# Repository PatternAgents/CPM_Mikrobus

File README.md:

CPM_Mikrobus Adaptor
====================

PatternAgents CPM_Mikrobus Adaptor

[  
*PatternAgents CPM_Mikrobus Adaptor*](http://www.patternagents.com/projects/CPM_Mikrobus.html)

The "CPM_Mikrobus Adaptor" board is designed to enable Cypress PSoC development boards to utilize Mikrobus peripherals.

The PatternAgents "CPM_Mikrobus Adaptor" board supports :

Cypress CY8CKIT-001 : (Supports up to three (3) "CPM_Mikrobus Adaptor")

Cypress CY8CKIT-030 : (Supports up to two (2) "CPM_Mikrobus Adaptor")

Cypress CY8CKIT-050 : (Supports up to two (2) "CPM_Mikrobus Adaptor")

Cypress CY3280-28xxx : (Supports one (1) "CPM_Mikrobus Adaptor")

Cypress CY3280-22x45 : (Supports one (1) "CPM_Mikrobus Adaptor")

(Not an Exhaustive list as more Cypress development boards are routinely released)

For information on Mikrobus peripherals, see http://www.mikroe.com/mikrobus/

[  
*Licensing CC BY-NC-SA 4.0*](http://creativecommons.org/licenses/by-nc-sa/4.0/)

PatternAgents uses the increasingly popular business model called "Dual Licensing" 
in which both the open source software distribution mechanism and traditional commercial software distribution models are combined.

Open Source Projects:        

If you are developing and distributing open source applications under the Creative Commons CC BY-NC-SA 4.0, 
as published by the Creative Commons Foundation, then you are free to use the PatternAgents hardware/software under the CC BY-NC-SA 4.0 license. 
Please note that CC BY-NC-SA 4.0 requires that all modifications to the original code as well as all Derivative Works 
must also be released under the terms of the CC BY-NC-SA 4.0 license.

Closed Source Projects:

If you are developing and distributing traditional closed source or commercial applications, 
you must purchase a PatternAgents commercial use license, 
which is specifically designed for users interested in retaining the proprietary status of their designs and code. 
All PatternAgents commercial licenses expressly supersede the CC BY-NC-SA 4.0 license. 
This means that when you license the PatternAgents software under a commercial license, 
you specifically do not use the software under the CC BY-NC-SA 4.0 license and therefore you are not subject to any of its terms.
        
If you would like to use our designs for your own personal or educational use, have at it! 

Our public design repository is available at <a href="https://github.com/patternagents">Github</a>.

If you would like to produce our designs for commercial use, or as products for sale, 
please contact us to arrange for a Commercial Use license. We have many other designs, 
as well as options and extras that are not released publicly. 
We will also customize designs, firmware, and software for a reasonable fee, just contact us to discuss your requirements.

THIS SOFTWARE IS PROVIDED BY THE CONTRIBUTORS "AS IS" AND WITHOUT ANY EXPRESS OR IMPLIED WARRANTIES, 
INCLUDING, BUT NOT LIMITED TO, THE IMPLIED WARRANTIES OF MERCHANTABILITY AND FITNESS FOR A PARTICULAR PURPOSE ARE DISCLAIMED. 
IN NO EVENT SHALL THE COPYRIGHT OWNER OR CONTRIBUTORS BE LIABLE FOR ANY DIRECT, INDIRECT, INCIDENTAL, SPECIAL, EXEMPLARY, 
OR CONSEQUENTIAL DAMAGES (INCLUDING, BUT NOT LIMITED TO, PROCUREMENT OF SUBSTITUTE GOODS OR SERVICES; LOSS OF USE, DATA, 
OR PROFITS; OR BUSINESS INTERRUPTION) HOWEVER CAUSED AND ON ANY THEORY OF LIABILITY, WHETHER IN CONTRACT, 
STRICT LIABILITY, OR TORT (INCLUDING NEGLIGENCE OR OTHERWISE) ARISING IN ANY WAY OUT OF THE USE OF THIS SOFTWARE, 
EVEN IF ADVISED OF THE POSSIBILITY OF SUCH DAMAGE. 

-------------------------------------------------------------------------------------------

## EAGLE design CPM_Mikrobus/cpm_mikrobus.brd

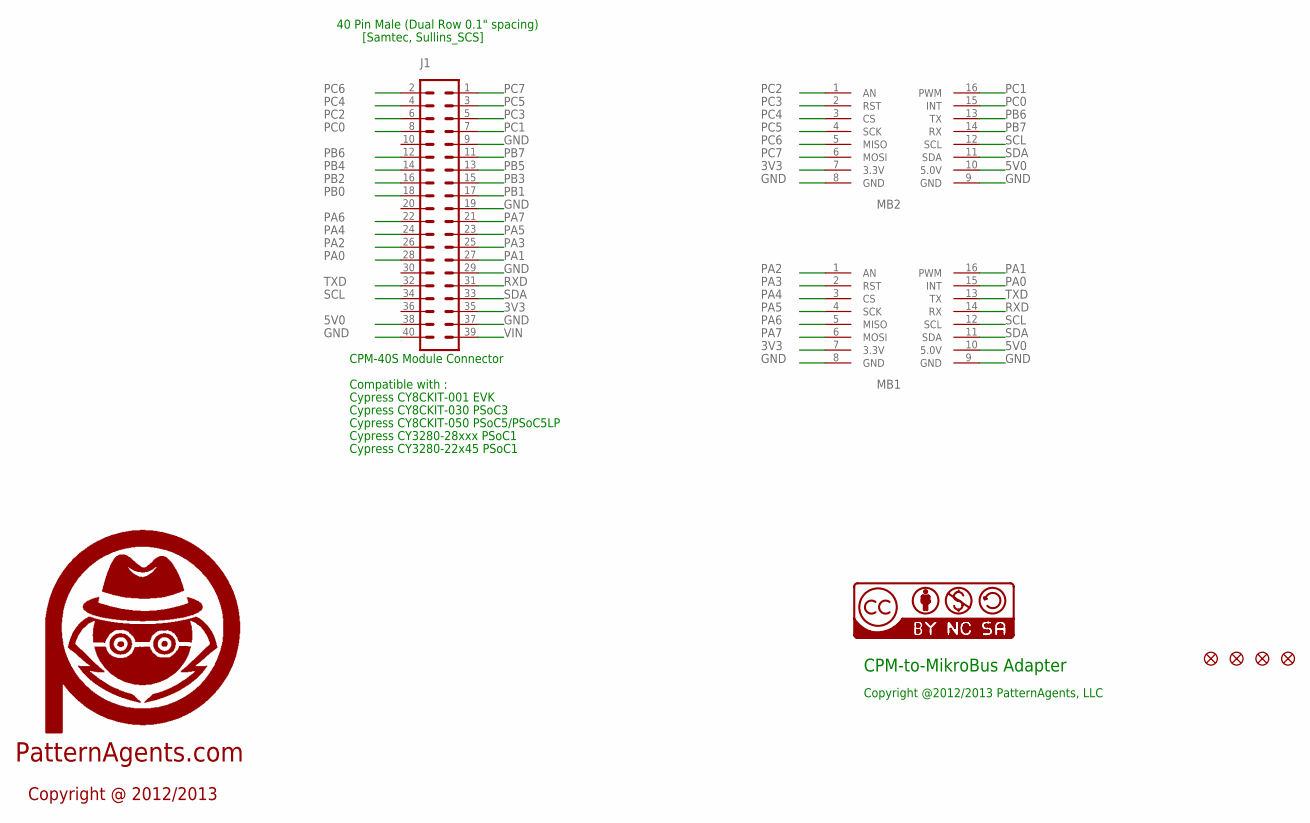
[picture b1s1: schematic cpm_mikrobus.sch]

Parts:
J1: SULLINS_SCS; MA20-2
JP1, JP2, JP3, JP4: FIDUCIAL1.5X3; FIDUCIAL-1.5X3
MB1, MB2: MIKROBUS_SOCKET
U$1: LOGO_PA_AGENTLARGE; LOGO_PA_AGENT_LARGE
U$2: BY_CC_SA_SYMNULL; NULL_SYM

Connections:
3V3: J1.35, MB1.7 (3.3V), MB2.7 (3.3V)
5V0: J1.38, MB1.10 (5.0V), MB2.10 (5.0V)
GND: J1.9, J1.19, J1.29, J1.37, J1.40, MB1.8 (GND), MB1.9 (GND), MB2.8 (GND), MB2.9 (GND)
PA0: J1.28, MB1.15 (INT)
PA1: J1.27, MB1.16 (PWM)
PA2: J1.26, MB1.1 (AN)
PA3: J1.25, MB1.2 (RST)
PA4: J1.24, MB1.3 (CS)
PA5: J1.23, MB1.4 (SCK)
PA6: J1.22, MB1.5 (MISO)
PA7: J1.21, MB1.6 (MOSI)
PB0: J1.18
PB1: J1.17
PB2: J1.16
PB3: J1.15
PB4: J1.14
PB5: J1.13
PB6: J1.12, MB2.13 (TX)
PB7: J1.11, MB2.14 (RX)
PC0: J1.8, MB2.15 (INT)
PC1: J1.7, MB2.16 (PWM)
PC2: J1.6, MB2.1 (AN)
PC3: J1.5, MB2.2 (RST)
PC4: J1.4, MB2.3 (CS)
PC5: J1.3, MB2.4 (SCK)
PC6: J1.2, MB2.5 (MISO)
PC7: J1.1, MB2.6 (MOSI)
RXD: J1.31, MB1.14 (RX)
SCL: J1.34, MB1.12 (SCL), MB2.12 (SCL)
SDA: J1.33, MB1.11 (SDA), MB2.11 (SDA)
TXD: J1.32, MB1.13 (TX)
VIN: J1.39

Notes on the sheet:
[Samtec, Sullins_SCS]
40 Pin Male (Dual Row 0.1" spacing)
CPM-40S Module Connector
Compatible with :
Cypress CY8CKIT-001 EVK
Cypress CY8CKIT-030 PSoC3
Cypress CY3280-28xxx PSoC1
Cypress CY3280-22x45 PSoC1
Cypress CY8CKIT-050 PSoC5/PSoC5LP
PatternAgents.com
Copyright @ 2012/2013
CPM-to-MikroBus Adapter
Copyright @2012/2013 PatternAgents, LLC

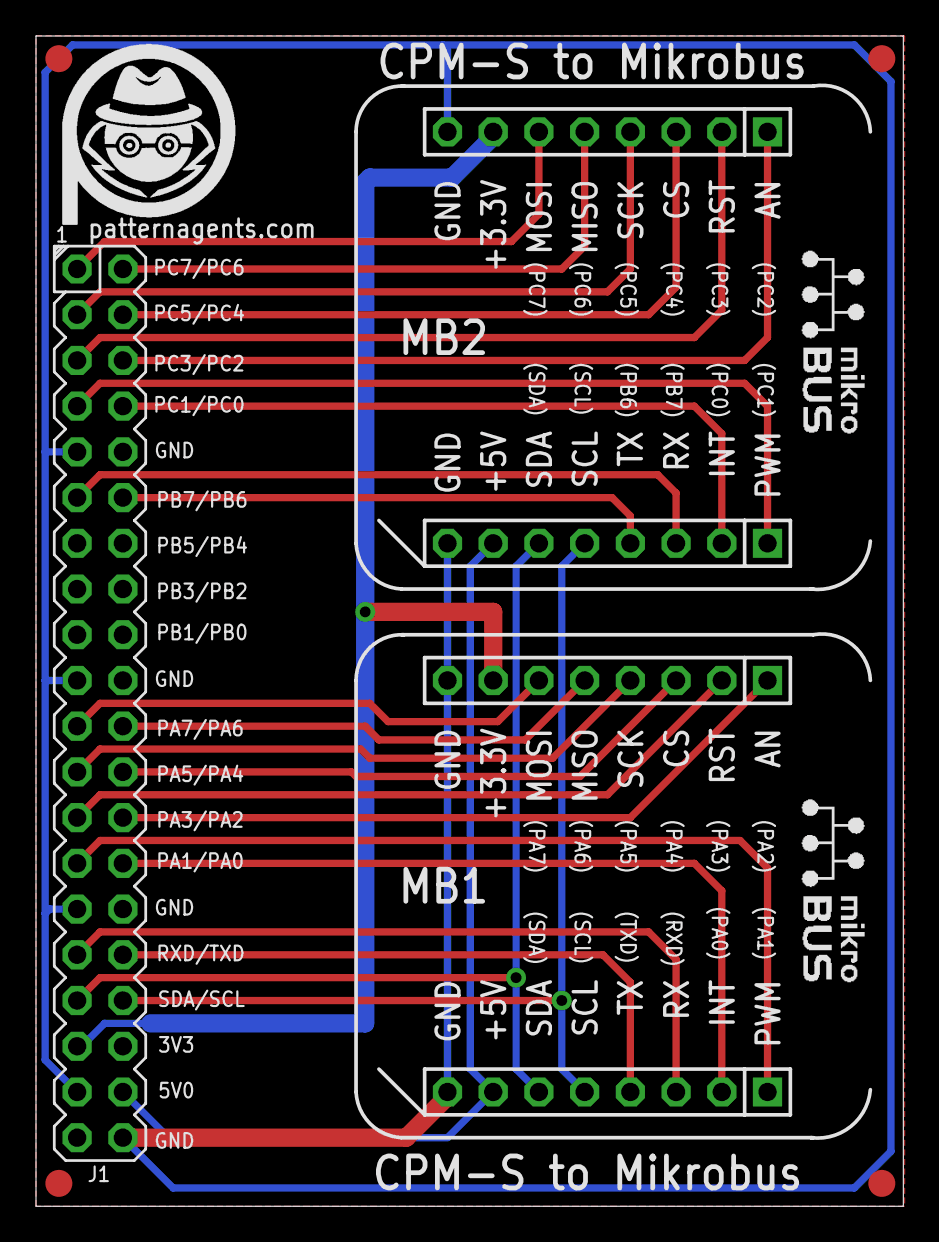
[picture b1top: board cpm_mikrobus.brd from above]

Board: 2 copper layers, 48.2 x 65.0 mm, 10 parts (1 on the bottom side), 25 nets.

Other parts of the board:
U$3: LOGO_PA_AGENTLARGE; LOGO_PA_AGENT_LARGE

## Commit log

2013-07-04 initial upload
2013-07-04 coreect image filenames
2013-07-15 fix image link
2013-07-18 add GPLv3 /Dual license files
2013-07-18 fix links
2013-07-18 Add Eagle design Files
2013-07-22 reduce png file sizes
2013-12-23 Move licensing to CC 4.0

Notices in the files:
parts and their libraries:
PatternAgents-Logos: License : http://creativecommons.org/licenses/by-sa/3.0
(Creative Commons 3.0)
PatternAgents-Logos: Source : http://wiki.creativecommons.org/CC_markers
PatternAgents-Logos: Released under the Creative Commons Attribution Share-Alike 3.0 License
